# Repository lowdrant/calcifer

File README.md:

# calcifer
Raspberry Pi Talking Fireplace

## Quick Start
1. Use AdaFruit's [MAX31856 breakout board](https://www.adafruit.com/product/3263) and a fire-resistant [thermocouple](https://www.adafruit.com/product/3245) setup.
2. Follow this [AdaFruit wiring guide](https://learn.adafruit.com/adafruit-max31856-thermocouple-amplifier/python-circuitpython) and connect `DRDY` to `Board D27` and `FAULT` to `Board D20`
3. Put the thermocouple in your fireplace
4. Connect a speaker to the RPI headphone jack
5. Run the following in the terminal:
```
> git clone https://github.com/lowdrant/calcifer.git
> sudo apt install python3-pip           # skip if pip3 installed
> cd calcifer
> ./install.sh                           # install dependencies
> sudo ./boot-setup.sh ADAFRUIT          # setup calcifer to run at boot (daemon)
> sudo systemctl start calcifer.service  # start daemon
> journatlctl -f -u calcifer.service     # stream log output
```

### Using with calciHATter PCB
calciHATter Pi HAT wiring is stored in the CALCIHATTER section of [calcifer.ini](calcifer.ini). After dependencies are installed, you only need to configure which config section Calcifer uses.
```
> sudo ./boot-setup.sh CALCIHATTER
> sudo systemctl restart calcifer.service
```

## Adding Sounds
Add .wav files to the [sounds/](sounds/) directory to add sounds for Calcifer. Calcifer plays a random .wav file from [sounds/](sounds/) when it detects a fire has started. This ensures Calcifer only plays a sound once rather than playing sounds constantly while a fire is going.

## Customizating Behavior and Pinout
[calcifer.ini](calcifer.ini) can be edited to configure entire hardware pinout and some program logic. It is parsed using Python3's `ConfigParser` object. After editing the config section the Calcifer daemon is using, run
```
> sudo systemctl restart calcifer.service
```
to reinitalize Calcifer with the new configuration. Since the config _section_ isn't changing, there's no need to resetup the daemon.

To change configuration sections (e.g. from ADAFRUIT to CALCIHATTER), run
```
> sudo ./boot-setup.sh <your-section>
```

### GPIO Configuration
GPIO values need to be of the form `board.XX` as if they are commands in a Python script because [calcifer.py](calcifer.py) uses `eval(<param>)` to configure GPIO objects. Look into CircuitPython for more details.

| Field       | Desc                       | Example     | Notes                               |
| ----------- | -------------------------- | ----------- | ----------------------------------- |
| spi         | Amplifier SPI bus          | board.SPI() | RPi SPI busses are weirdly specific |
| cs          | Amplifier chip select      | board.D22   | Digital Output                      |
| drdy        | Amplifier data ready pin   | board.D27   | Digital Input                       |
| tc_fault    | Amplifier fault pin        | board.D3    | Digital Input                       |
| tc_reset    | Amplifier power switch pin | board.D26   | Digital Output                      |
| soundswitch | Toggle sound playing       | board.D2    | Digital Input; play sound if high   |
| hbeat       | Heartbeat LED              | board.D21   | Digital Output                      |
| fault       | Fault indicator LED        | board.D20   | Digital Output                      |

### Temperature Logic
Configure temperature sensor type, active/inactive temperature thresholds, and data reading frequency. `thresh` and `off_thresh` introduce hysterisis

| Field      | Desc                            | Example | Notes                                |
| ---------- | ------------------------------- | ------- | ------------------------------------ |
| tctype     | Thermocouple type               | K       | `adafruit_max31856.ThermocoupleType` |
| thresh     | threshold for fire-on state     | 100     | degC float                           |
| off_thresh | threshold for fire-off state    | 50      | degC float; must be less than thresh |
| T_read     | sample period in fire-off state | 1       | seconds                              |
| T_going    | sample period in fire-on state  | 10      | seconds                              |

### Misc Behavior
This does not affect the user experience.
| Field              | Desc                         | Example   | Notes                 |
| ------------------ | ---------------------------- | --------- | --------------------- |
| host               | Host for daemon stop command | 127.0.0.1 | host must be RPi      |
| port               | Port for daemon stop command | 10000     |                       |
| loglevel           | log level to stdout          | DEBUG     | logging library value |
| drdy_count_timeout | Timeout for amp power cycle  | 3         | int                   |
| T_hbeat            | Heartbeat period             | 2         | seconds               |

## Design Overview
### Hardware
The calciHATter PCB conforms to the Raspberry Pi HAT standard. It is a bare-bones PCB that allows a Pi to interface with the MAX31856 over SPI, a sound switch for enabling/disabling Calcifer, debug LEDs, and the configuration EEPROM. Its documentation, fabrication files, and bill of materials can be found in [calciHATter/](calciHATter/). It was designed in KiCAD. I do not provide a means to program the HAT EEPROM with pinout information.

### Software
The Calcifer daemon simply calls [calcifer.py](calcifer.py) with appropriate command line arguments.
[boot-setup.sh](boot-setup.sh) provides a CLI to automatically configure `calcifer.service` for SystemD.

Calcifer program logic is packaged as an object inside a CLI script to run the Calcifer mainloop in a clean, stateful way while also providing a basic testing/characterization interface for thermocouple evaluation and debugging.

The Calcifer object uses 3 threads in its mainloop
1. `_run`, which measures temperature and plays sound if fire goes from off to on
2. `_hbeat`, which blinks the heartbeat LED
3. `_listen`, which listens for a shutdown command on `host:port` and joins the mainllop threads on receipt of said shutdown command

### Fixing Sound Issues
Some PyGame dependencies need to be built from source (namely LibSDL2) for unknown reasons. `install.sh` should handle this, but if you are still getting sound issues, run the below to install the dependencies directly.
```
> ./install-pygame-deps.sh
```

## Author
Marion Anderson - [lmanderson42@gmail.com](mailto:lmanderson42@gmail.com)

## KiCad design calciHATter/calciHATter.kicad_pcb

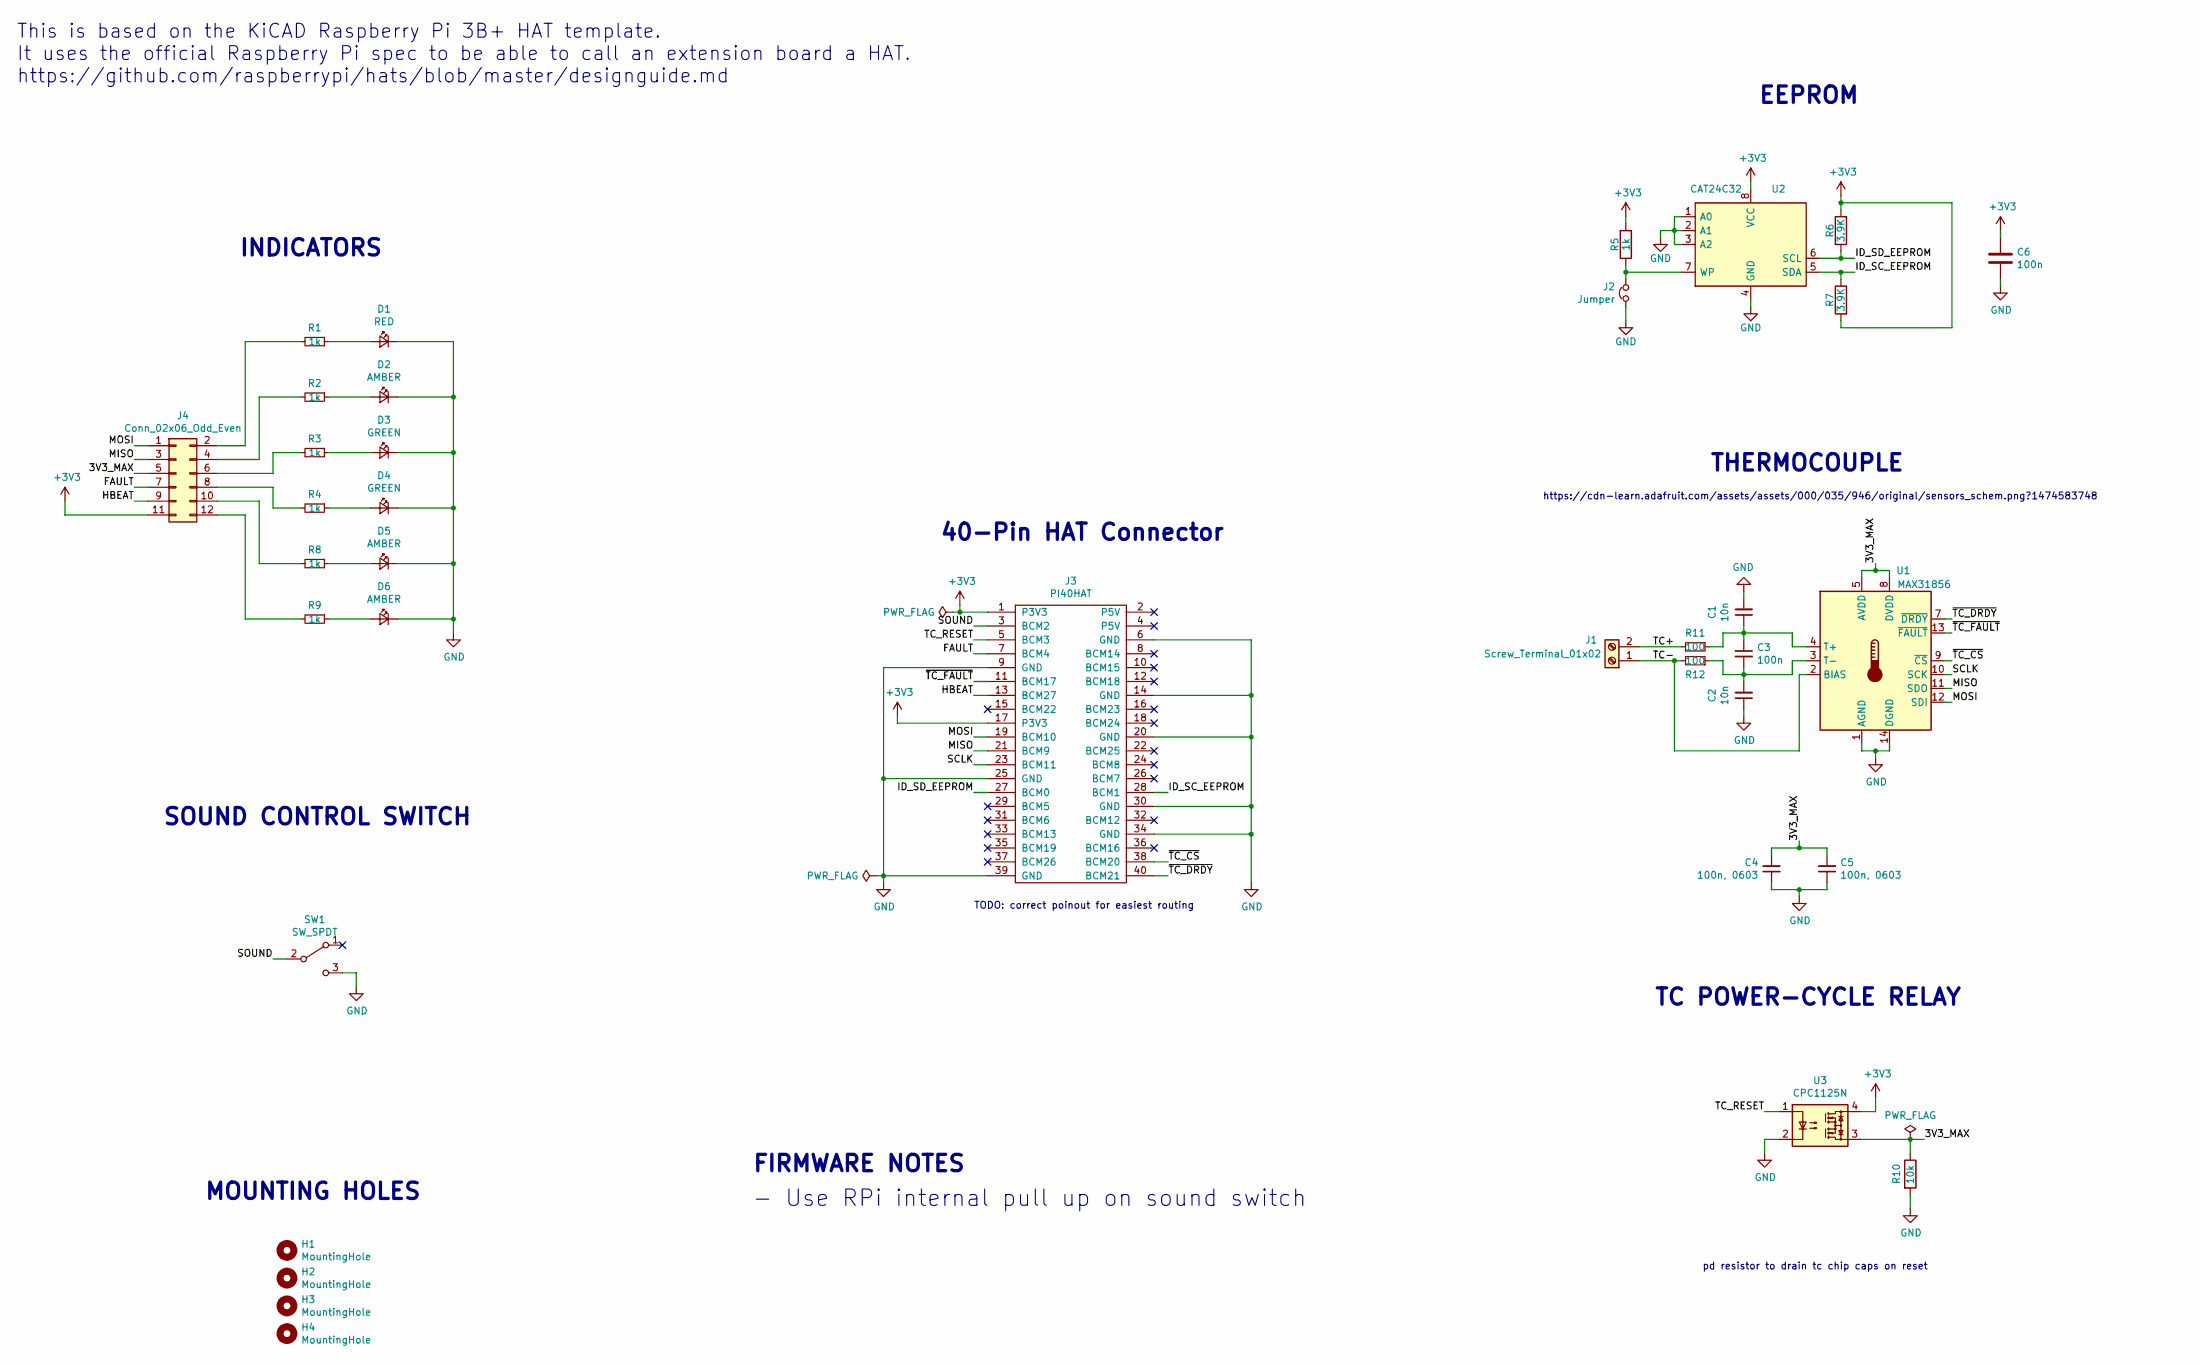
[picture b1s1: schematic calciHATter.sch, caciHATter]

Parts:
C1, C2: 10n; C_0603_1608Metric_Pad1.05x0.95mm_HandSolder
C3, C6: 100n; C_0603_1608Metric_Pad1.05x0.95mm_HandSolder
C4, C5: 100n, 0603; C_0603_1608Metric_Pad1.05x0.95mm_HandSolder
D1: RED; LED_0603_1608Metric_Pad1.05x0.95mm_HandSolder
D2, D5, D6: AMBER; LED_0603_1608Metric_Pad1.05x0.95mm_HandSolder
D3, D4: GREEN; LED_0603_1608Metric_Pad1.05x0.95mm_HandSolder
H1, H2, H3, H4: MountingHole; MountingHole_2.7mm_M2.5_DIN965
J1: Screw_Terminal_01x02; TerminalBlock_Phoenix_MKDS-1,5-2_1x02_P5.00mm_Horizontal
J2: Jumper; PinHeader_1x02_P2.54mm_Vertical
J3: PI40HAT; PinSocket_2x20_P2.54mm_Vertical
J4: Conn_02x06_Odd_Even; PinHeader_2x06_P2.54mm_Vertical
R1, R2, R3, R4, R5, R8, R9: 1k; R_0603_1608Metric_Pad1.05x0.95mm_HandSolder
R6, R7: 3.9K; R_0603_1608Metric_Pad0.84x1.00mm_HandSolder
R10: 10k; R_0603_1608Metric_Pad1.05x0.95mm_HandSolder
R11, R12: 100; R_0603_1608Metric_Pad1.05x0.95mm_HandSolder
SW1: SW_SPDT; PinHeader_1x03_P2.54mm_Vertical
U1: MAX31856; TSSOP-14_4.4x5mm_P0.65mm
U2: CAT24C32; SOIC-8_3.9x4.9mm_P1.27mm
U3: CPC1125N; SOP-4_3.8x4.1mm_P2.54mm

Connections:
+3V3: C6.1, J3.1 (P3V3), J3.17 (P3V3), J4.11, R5.2, R6.2, R7.2, U2.8 (VCC), U3.4
/3V3_MAX: C4.2, C5.2, J4.5, R10.1, U1.5 (AVDD), U1.8 (DVDD), U3.3
/FAULT: J3.7 (BCM4), J4.7
/HBEAT: J3.13 (BCM27), J4.9
/ID_SC_EEPROM: J3.28 (BCM1), R7.1, U2.5 (SDA)
/ID_SD_EEPROM: J3.27 (BCM0), R6.1, U2.6 (SCL)
/MISO: J3.21 (BCM9), J4.3, U1.11 (SDO)
/MOSI: J3.19 (BCM10), J4.1, U1.12 (SDI)
/SCLK: J3.23 (BCM11), U1.10 (SCK)
/SOUND: J3.3 (BCM2), SW1.2 (B)
/TC+: J1.2, R11.2
/TC-: J1.1, R12.2, U1.2 (BIAS)
/TC_RESET: J3.5 (BCM3), U3.1
/~TC_CS: J3.38 (BCM20), U1.9 (~CS)
/~TC_DRDY: J3.40 (BCM21), U1.7 (~DRDY)
/~TC_FAULT: J3.11 (BCM17), U1.13 (~FAULT)
GND: C1.2, C2.1, C4.1, C5.1, C6.2, D1.1 (K), D2.1 (K), D3.1 (K), D4.1 (K), D5.1 (K), D6.1 (K), J2.2, J3.6 (GND), J3.9 (GND), J3.14 (GND), J3.20 (GND), J3.25 (GND), J3.30 (GND), J3.34 (GND), J3.39 (GND), R10.2, SW1.3 (C), U1.1 (AGND), U1.14 (DGND), U2.1 (A0), U2.2 (A1), U2.3 (A2), U2.4 (GND), U3.2
unnamed: C1.1, C3.1, R11.1, U1.4 (T+)
unnamed: C2.2, C3.2, R12.1, U1.3 (T-)
unnamed: D1.2 (A), R1.1
unnamed: D2.2 (A), R2.1
unnamed: D3.2 (A), R3.1
unnamed: D4.2 (A), R4.1
unnamed: D5.2 (A), R8.1
unnamed: D6.2 (A), R9.1
unnamed: J2.1, R5.1, U2.7 (WP)
unnamed: J4.2, R1.2
unnamed: J4.4, R2.2
unnamed: J4.6, R3.2
unnamed: J4.8, R4.2
unnamed: J4.10, R8.2
unnamed: J4.12, R9.2

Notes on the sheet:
This is based on the KiCAD Raspberry Pi 3B+ HAT template. It uses the official Raspberry Pi spec to be able to call an extension board a HAT. https://github.com/raspberrypi/hats/blob/master/designguide.md
MOUNTING HOLES
40-Pin HAT Connector
THERMOCOUPLE
EEPROM
INDICATORS
TC POWER-CYCLE RELAY
TODO: correct poinout for easiest routing
pd resistor to drain tc chip caps on reset
https://cdn-learn.adafruit.com/assets/assets/000/035/946/original/sensors_schem.png?1474583748
SOUND CONTROL SWITCH
- Use RPi internal pull up on sound switch
FIRMWARE NOTES

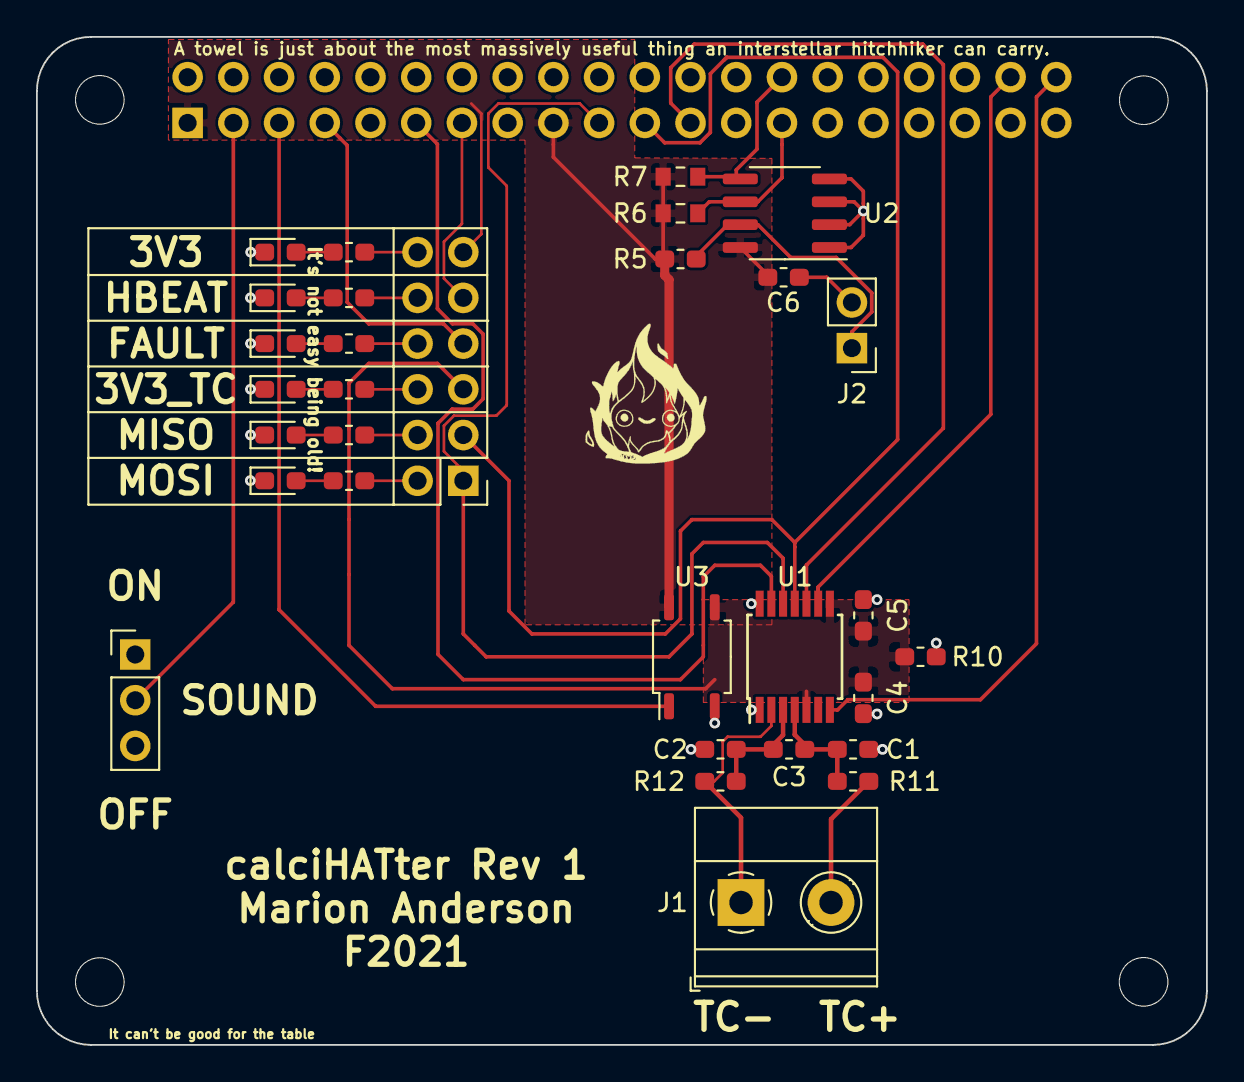
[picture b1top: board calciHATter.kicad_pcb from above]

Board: 2 copper layers, 65.0 x 56.0 mm, 36 parts (1 on the bottom side), 32 nets.

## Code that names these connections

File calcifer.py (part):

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    ---------
    cs          - TC amplifier chip select pins
    drdy        - TC amplifier data ready pin
    hbeat       - heartbeat LED pin
    tc_reset    - TC power supply relay pin
    fault       - fault LED
    soundswitch - sound control pin input
    """
    def  __init__(self, fnconf=None, section='DEFAULT', **kwargs):
        # Config Setup
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        # TC Reset Relay Setup
        self.tc_reset = dioDigitalInOut(eval(conf[section]['tc_reset']))
        self.tc_reset.direction = dioDirection.OUTPUT
        self.tc_reset.value = 0

        # Indicator LED Setup
        self.hbeat = dioDigitalInOut(eval(conf[section]['hbeat']))
        self.hbeat.direction = dioDirection.OUTPUT
        self.hbeat.value = 0
        self.fault = dioDigitalInOut(eval(conf[section]['fault']))
        self.fault.direction = dioDirection.OUTPUT
        self.fault.value = 0
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        while self.go:
            try:
                if self.tc_fault.value == 0:
                    self.logger.critical(f'tc_fault pin low')

                self.update_tempbuf()
                self.logger.debug(f'tempbuf:{self.tempbuf}')
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        while self.go:
            self.hbeat.value = not self.hbeat.value if (self.T_hbeat>0) else 0  # no hbeat case
            sleep(self.T_hbeat)
        self.hbeat.hbeat = 0  # turn off led when ending program
        self.logger.debug(f'hbeat thread exited. go:{self.go}')

    def start(self):
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
    def _wrapup(self):
        """Release resources + turn off relay/leds."""
        self.hbeat.value = 0
        self.tc_reset.value = 0
        try:
            self.sock.close()
        except sock_error as e:
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
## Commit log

2021-06-10 Add Python to .gitignore
2021-06-10 started a HAT. not totally sure if it's worth the effort
2021-08-22 started temperature & thread inteface
2021-09-26 Start of TC testing CLI in jobs.py
2021-09-27 Working tc measurment + characterization interface
2021-09-27 Added sound playing functionality
2021-09-27 Dependency improvements for playsound
2021-09-28 Improved code/cli structure; moving to bgnd process
2021-09-28 Switched to PyGame for sound
2021-09-28 code cleanup; prep for signal handling
2021-09-29 Working socket-based thread killer. TODO: figure out why pygame isn't working
2021-09-29 added indicator led functionality
2021-09-29 added relay toggle delay to config file
2021-09-29 Amended install script with working pygame.mixer
2021-09-30 Implemented logging scheme
2021-09-30 Added tc chip reset condition + more logging
2021-09-30 added digital input to turn off playing of sound
2021-10-01 PCB placement to include indicators and toggle switch
2021-10-01 continued layout, some routing & pinout changes
2021-10-01 Finalized pinout, routing. TODO: cleanup+ERC
2021-10-02 finalized schematic+routing. need easter eggs and footprint checks
2021-10-02 release calciHATter rev 1 for fab
2021-10-03 config file now matches pcb pinout. installation cleanup
2021-10-06 Calcifer sound bites
2021-10-21 cleaned up mainloop exception handling
2021-11-13 major README update; other docs
2021-11-13 added pcb net file
2021-11-13 Scripting to create a calcifer service
2021-11-13 install.sh now says if pygame deps already installed
2021-11-13 working service daemon
2021-11-13 minor readme updates
2021-11-13 cleaner quickstart docs
2021-11-13 README table cleanup
2021-11-16 reformat log messages for journalctl
2021-11-17 Minor README clarity edits
2021-11-17 boot-setup.sh no longer restarts calcifer.service
2021-11-17 calcifer py/ini robustness edits
2021-11-17 pcb photo to readme
2021-11-18 Calcifer class attribute documentation
2021-11-18 in-situ fireplace updates
2022-01-28 corrected thermocouple fault detection gpio; more robust thread joining
2022-01-28 improved state logging; added fireplace params; maybe resolved also underrun bug
2022-01-29 corrected fault pin configuration; added socket fail-to-close error messages
2022-05-12 add play sound utility
